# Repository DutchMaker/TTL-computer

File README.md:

# 74xx Computer

My attempt at building a computer from scratch with 74xxx logic chips.  

## Project Shelved!

I have abandoned this project, but only to reboot it with a different approach.  
Make sure to check **[The DM-02 Computer](https://github.com/DutchMaker/DM-02)** which is my second attempt at a computer from scratch!

## Status as of September 4th, 2019:

[**General architecture**](https://github.com/DutchMaker/TTL-computer/blob/master/Documentation/Architecture.pdf) has been worked out as high level schematic.  

Worked on **instruction set, micro code, module documentation & general notes** from time to time (see: [Documentation](https://github.com/DutchMaker/TTL-computer/tree/master/Documentation)). Only thing missing right now is some documentation on each of the modules. 

The entire computer has been built in [**Logisim**](https://github.com/DutchMaker/TTL-computer/tree/master/Documentation/Logisim) to verify that the way I had everything in mind is actually going to work.

I've built a [**microcode compiler**](https://github.com/DutchMaker/TTL-computer/tree/master/Code/Microcode) for the Controller's ROM image. This takes a source file which defines all the microcode and compiles it into a binary image that is loaded into the microcode ROM.

The 74xx Computer's **instruction set** has been implemented, its **[assembly language](https://github.com/DutchMaker/TTL-computer/blob/master/Documentation/74xx-Assembly-Language.md)** is fully documented and I've built an [**assembler**](https://github.com/DutchMaker/TTL-computer/tree/master/Code/Assembler) to convert assembly programs to machine code.

[**Circuit diagrams and PCBs**](https://github.com/DutchMaker/TTL-computer/tree/master/Circuits) have all been designed in KiCad and have been or are currently being produced:

- [x] Clock (*built and tested*)
- [x] Registers (*built and tested*)
- [x] ALU (*built and tested*)
- [x] Program Counter (*built and tested*)
- [x] Stack Pointer (*built and tested*)
- [x] Flags register (*built and tested*)
- [x] Memory (*built and tested*)
- [x] Memory Access Register (*built and tested*)
- [ ] Controller (*redesigned circuit to account for reset ciruitry - waiting for PCB production*)
- [x] Main Board ( *built and tested*)

## TODO's / Plans:

- Build the computer in real life (**IN PROGRESS**)
  - First revision is based on separate PCBs that are all connected together by one large main PCB.
  - If all works out, there may be a second revision will be one large PCB that contains all modules as one circuit.
- Write additional/updated documentation on all modules.

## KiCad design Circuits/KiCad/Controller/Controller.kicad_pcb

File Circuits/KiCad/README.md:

# KiCad projects

- Add `./Libraries/74xx-Computer-Symbols.lib` as global Symbol library to KiCad (Eeschema)
- Add `./Libraries` as global Footprint library to KiCad (Pcbnew)
- PCBs are initially autorouted using `./Libraries/freeRouting.jar` and traces are enhanced manually

### Known deviations/errors in current Schematic/PCB files

There are a number of deviations and errors that were found in schematic/PCB designs after PCB production. They are listed here if they were not fixed in the schematic/PCB design files.

- **ALU:** LED bar graph for AX (_BAR1_) and AY (_BAR2_) have swapped places on the PCB.
- **ALU:** Cn input needs to be inverted.
- This is added to the main board because ALU PCB was already produced and there were no available NOT gates available.
- **ALU:** Outer margin varies from other boards.
- **Flags Register:** U6 and U7 (74x74) ~PRE pins (4 and 10) are floating. They must be tied to +5V otherwise the chip does not function properly.
- **Memory & Memory Access Register:** The switches used for SW1 to SW8 briefly short out the circuit while switching. This reset the entire computer. Solved this by removing the connection to ground and adding 10k pull-down resistors between the data lines and ground.
- **Memory:** RAM should write when clock pulse is high. Otherwise manual input is difficult because that relies on single stepping the clock. Solved this by feeding the clock signal through U1 (74x04) before connecting it to U4A (74x32).
- **Main Board:** Current main board PCB design does not fit the current instruction register PCB - only the improvised one that I've built.
- **Controller:** U9 (74x74) ground pin is not connected. Also ~PRE pin (4) is floating and must be tied to +5V.
- **Controller & Memory**: Drill holes for ZIF socket are too narrow (need to be 1mm).
- **Main Board:** Forgot to add LED bar to display data bus contents.
- **Main Board:** Forgot to add one or more expansion ports.
- **Main Board:** Need pull-down resistors on the data bus
- **Controller**: There is an issue with powering up the controller: its initial state has all control lines enabled. This messes up the state of other modules.
  - Needs pull-down/up resistors on control lines for initial state of modules (reset state) - this is improvised on the main board now. We also must have a boot/reset procedure, something like: 
    - First all control line output is high impedance (this resets all modules because of the pull-down/up resistors that determine initial state). Will probably do this by cutting power to the controller during boot.
    - Then the controller is powered up and it needs to load microcode address 0
    - Then it can start processing instructions

### Suggested improvements

- Clock: Use a bigger push switch for single stepping
  - Add a *continue* option in order to continue execution after a HALT instruction.
- When all modules are built and tested, combine them into a single PCB.
  - I may decide to never do this and just start designing the next version of the CPU.
- Add decoupling caps (have only been added to main board now)
- Improve silk screen documentation
- Databus LEDs missing on Main Board
- Add hex decoders to registers / memory.
  - Add switch to disable output?
- ADC and SUBC instructions should take the carry flag into account
  - SUBC may be renamed to SUBB (borrow)

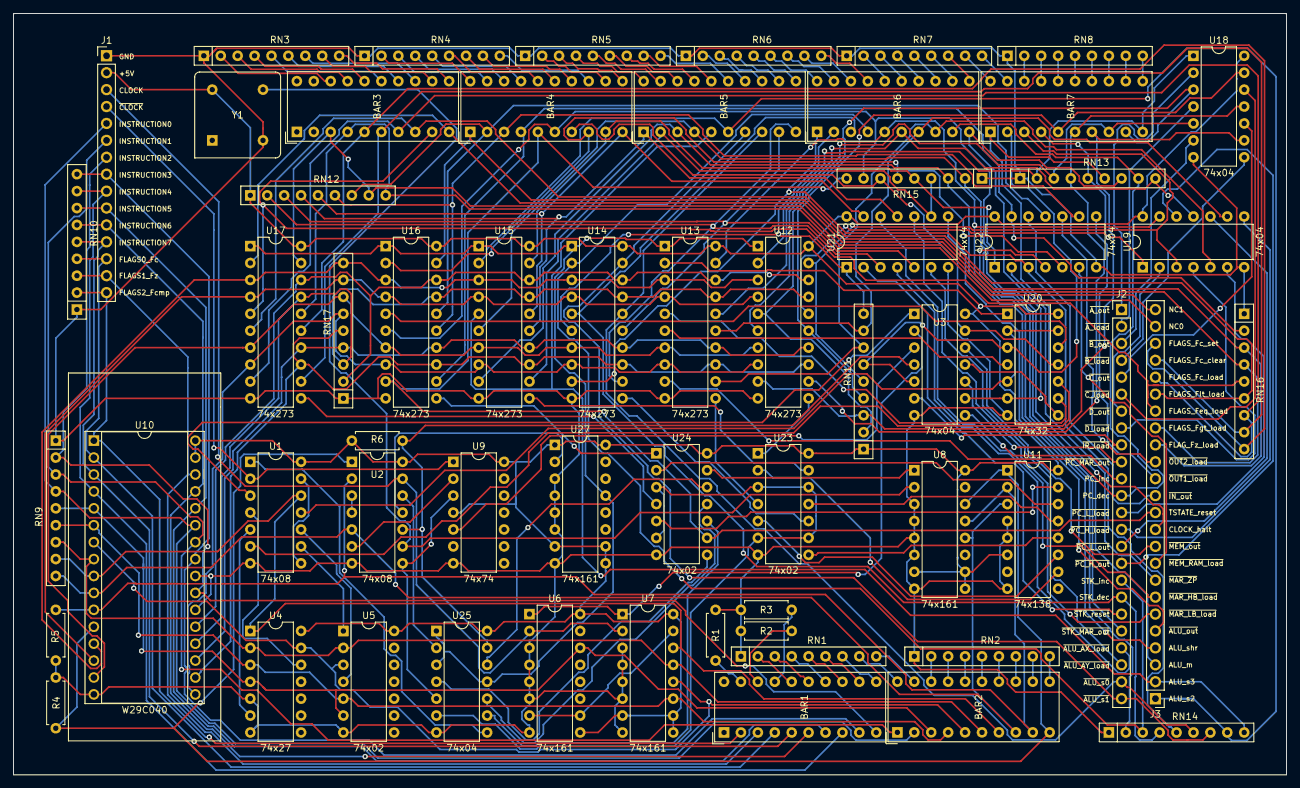
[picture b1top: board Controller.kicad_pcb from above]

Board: 2 copper layers, 191.1 x 114.3 mm, 60 parts (0 on the bottom side), 216 nets.

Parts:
BAR1, BAR2, BAR3, BAR4, BAR5, BAR6, BAR7: HDSP-4830_2; Bar-Graph-10
J1: Conn_01x15_Male; PinHeader_1x15_P2.54mm_Vertical
J2, J3: Conn_01x24_Male; PinHeader_1x24_P2.54mm_Vertical
R1, R2, R4, R5: R; R_Axial_DIN0207_L6.3mm_D2.5mm_P7.62mm_Horizontal
R3: 470; R_Axial_DIN0207_L6.3mm_D2.5mm_P7.62mm_Horizontal
R6: 10K; R_Axial_DIN0207_L6.3mm_D2.5mm_P7.62mm_Horizontal
RN1, RN2, RN3, RN4, RN5, RN6, RN7, RN8: 470; R_Array_SIP9
RN9, RN10, RN11, RN12, RN13, RN14, RN15, RN16, RN17: 10K; R_Array_SIP9
U1, U2: 74x08; DIP-14_W7.62mm
U3, U18, U19, U21, U22, U25: 74x04; DIP-14_W7.62mm
U4: 74x27; DIP-14_W7.62mm
U5, U23, U24: 74x02; DIP-14_W7.62mm
U6, U7, U8, U27: 74x161; DIP-16_W7.62mm
U9: 74x74; DIP-14_W7.62mm
U10: W29C040; ZIF-32_Socket
U11: 74x138; DIP-16_W7.62mm
U12, U13, U14, U15, U16, U17: 74x273; DIP-20_W7.62mm
U20: 74x32; DIP-14_W7.62mm
Y1: 8 MHz (max. 10 MHz); Oscillator_DIP-8_v2

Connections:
+5V: J1.2, R6.1, RN11.1, RN12.1, U1.14, U2.14, U3.14, U4.14, U5.14, U6.9, U6.16, U7.7, U7.9, U7.10, U7.16, U8.7, U8.9, U8.10, U8.16, U9.4, U9.14, U10.31, U10.32, U11.6, U11.16, U12.20, U13.20, U14.20, U15.20, U16.20, U17.20, U18.14, U19.14, U20.14, U21.14, U22.14, U23.14, U24.14, U25.14, U27.1, U27.7, U27.9, U27.10, U27.16, Y1.1
ALU_AX_load: BAR5.10, RN12.2, U14.12, U21.3
ALU_AY_load: BAR5.9, RN12.3, U14.15, U21.5
ALU_m: BAR5.4, J3.3, RN15.2, U15.6
ALU_out: BAR5.2, RN15.4, U15.12, U21.9
ALU_s0: BAR5.8, J2.23, RN14.6, U14.16
ALU_s1: BAR5.7, J2.24, RN14.7, U14.19
ALU_s2: BAR5.6, J3.1, RN14.8, U15.2
ALU_s3: BAR5.5, J3.2, RN14.9, U15.5
ALU_shr: BAR5.3, J3.4, RN15.3, U15.9
A_load: BAR7.9, RN11.2, U12.5, U18.3
A_out: BAR7.10, RN13.2, U12.2, U18.1
BANK0: BAR2.10, R4.1, U2.1, U8.14, U10.12, U11.1
BANK1: BAR2.9, R5.1, U2.2, U8.13, U10.11, U11.2
BANK2: BAR2.8, RN9.9, U2.5, U8.12, U10.10, U11.3
B_load: BAR7.7, RN11.3, U12.9, U18.9
B_out: BAR7.8, RN13.3, U12.6, U18.5
CLOCK: J1.3, U2.13, U6.2, U7.2
CLOCK_INTERNAL: U2.9, U8.2, Y1.3
CLOCK_halt: BAR4.6, J3.11, RN15.8, U16.6
C_load: BAR7.5, RN11.4, U12.15, U18.13
C_out: BAR7.6, RN13.4, U12.12, U18.11
DATA0: RN17.9, U10.13, U12.3, U13.3, U14.3, U15.3, U16.3, U17.3
DATA1: RN17.8, U10.14, U12.4, U13.4, U14.4, U15.4, U16.4, U17.4
DATA2: RN17.7, U10.15, U12.7, U13.7, U14.7, U15.7, U16.7, U17.7
DATA3: RN17.6, U10.17, U12.8, U13.8, U14.8, U15.8, U16.8, U17.8
DATA4: RN17.5, U10.18, U12.13, U13.13, U14.13, U15.13, U16.13, U17.13
DATA5: RN17.4, U10.19, U12.14, U13.14, U14.14, U15.14, U16.14, U17.14
DATA6: RN17.3, U10.20, U12.17, U13.17, U14.17, U15.17, U16.17, U17.17
DATA7: RN17.2, U10.21, U12.18, U13.18, U14.18, U15.18, U16.18, U17.18
D_load: BAR7.3, RN11.5, U12.19, U19.3
D_out: BAR7.4, RN13.5, U12.16, U19.1
EN0: U11.10, U23.2
EN1: U11.11, U23.5
EN2: U11.12, U23.8
EN3: U11.13, U23.11
EN4: U11.14, U24.2
EN5: U11.15, U24.5
FLAGS0_Fc: BAR1.4, J1.13, RN10.4, U10.2
FLAGS1_Fz: BAR1.3, J1.14, RN10.3, U10.30
FLAGS2_Fcmp: BAR1.2, J1.15, RN10.2, U10.1
FLAGS_Fc_clear: BAR3.6, J3.21, RN16.8, U17.12
FLAGS_Fc_load: BAR3.7, J3.20, RN16.7, U17.9
FLAGS_Fc_set: BAR3.5, J3.22, RN16.9, U17.15
FLAGS_Feq_load: BAR3.9, J3.18, RN16.5, U17.5
FLAGS_Fgt_load: BAR3.10, J3.17, RN16.4, U17.2
FLAGS_Flt_load: BAR3.8, J3.19, RN16.6, U17.6
FLAGS_Fz_load: BAR4.1, J3.16, RN16.3, U16.19
GND: J1.1, R1.1, R2.1, R3.1, R4.2, R5.2, RN1.1, RN2.1, RN3.1, RN4.1, RN5.1, RN6.1, RN7.1, RN8.1, RN9.1, RN10.1, RN13.1, RN14.1, RN15.1, RN16.1, RN17.1, U1.7, U2.7, U3.7, U4.5, U4.7, U5.7, U6.3, U6.4, U6.5, U6.6, U6.8, U7.3, U7.4, U7.5, U7.6, U7.8, U8.3, U8.4, U8.5, U8.6, U8.8, U9.7, U10.16, U10.22, U10.24, U11.4, U11.5, U11.8, U12.10, U13.10, U14.10, U15.10, U16.10, U17.10, U18.7, U19.7, U20.7, U21.7, U22.7, U23.7, U24.7, U25.7, U27.3, U27.4, U27.5, U27.6, U27.8, Y1.2
INSTRUCTION0: BAR2.2, J1.5, RN9.4, U10.27
INSTRUCTION1: BAR2.1, J1.6, RN9.3, U10.26
INSTRUCTION2: BAR1.10, J1.7, RN9.2, U10.23
INSTRUCTION3: BAR1.9, J1.8, RN10.9, U10.25
INSTRUCTION4: BAR1.8, J1.9, RN10.8, U10.4
INSTRUCTION5: BAR1.7, J1.10, RN10.7, U10.28
INSTRUCTION6: BAR1.6, J1.11, RN10.6, U10.29
INSTRUCTION7: BAR1.5, J1.12, RN10.5, U10.3
IN_out: BAR4.4, RN16.2, U16.12, U22.13
IR_load: U13.2, U20.1
IR_load_LED: BAR7.2, RN11.6, U3.5, U20.3
MAR_HB_load: BAR4.10, RN12.5, U15.16, U21.13
MAR_LB_load: BAR5.1, RN12.4, U15.15, U21.11
MAR_ZP: BAR4.9, RN15.5, U15.19, U22.1
MEM_RAM_load: BAR4.8, RN15.6, U16.2, U22.5
MEM_out: U16.5, U20.12
MEM_out_LED: BAR4.7, RN15.7, U3.13, U20.11
NC0: BAR3.4, J3.23, RN12.9, U17.16
NC1: BAR3.3, J3.24, RN12.8, U17.19
unnamed: BAR1.11, RN1.7
unnamed: BAR1.12, RN1.6
unnamed: BAR1.13, RN1.5
unnamed: BAR1.14, RN1.4
unnamed: BAR1.15, RN1.3
unnamed: BAR1.16, RN1.2
unnamed: BAR1.17, R3.2
unnamed: BAR1.18, R2.2
unnamed: BAR1.19, R1.2
unnamed: BAR2.11, RN2.9
unnamed: BAR2.12, RN2.8
unnamed: BAR2.13, RN2.7
unnamed: BAR2.14, RN2.6
unnamed: BAR2.15, RN2.5
unnamed: BAR2.16, RN2.4
unnamed: BAR2.17, RN2.3
unnamed: BAR2.18, RN2.2
unnamed: BAR2.19, RN1.9
unnamed: BAR2.20, RN1.8
unnamed: BAR3.11, RN3.9
unnamed: BAR3.12, RN3.8
unnamed: BAR3.13, RN3.7
unnamed: BAR3.14, RN3.6
unnamed: BAR3.15, RN3.5
unnamed: BAR3.16, RN3.4
unnamed: BAR3.17, RN3.3
unnamed: BAR3.18, RN3.2
unnamed: BAR4.11, RN5.3
unnamed: BAR4.12, RN5.2
unnamed: BAR4.13, RN4.9
unnamed: BAR4.14, RN4.8
unnamed: BAR4.15, RN4.7
unnamed: BAR4.16, RN4.6
unnamed: BAR4.17, RN4.5
unnamed: BAR4.18, RN4.4
unnamed: BAR4.19, RN4.3
unnamed: BAR4.20, RN4.2
unnamed: BAR5.11, RN6.5
unnamed: BAR5.12, RN6.4
unnamed: BAR5.13, RN6.3
unnamed: BAR5.14, RN6.2
unnamed: BAR5.15, RN5.9
unnamed: BAR5.16, RN5.8
unnamed: BAR5.17, RN5.7
unnamed: BAR5.18, RN5.6
unnamed: BAR5.19, RN5.5
unnamed: BAR5.20, RN5.4
unnamed: BAR6.11, RN7.7
unnamed: BAR6.12, RN7.6
unnamed: BAR6.13, RN7.5
unnamed: BAR6.14, RN7.4
unnamed: BAR6.15, RN7.3
unnamed: BAR6.16, RN7.2
unnamed: BAR6.17, RN6.9
unnamed: BAR6.18, RN6.8
unnamed: BAR6.19, RN6.7
unnamed: BAR6.20, RN6.6
unnamed: BAR7.11, RN8.9
unnamed: BAR7.12, RN8.8
unnamed: BAR7.13, RN8.7
unnamed: BAR7.14, RN8.6
unnamed: BAR7.15, RN8.5
unnamed: BAR7.16, RN8.4
unnamed: BAR7.17, RN8.3
unnamed: BAR7.18, RN8.2
unnamed: BAR7.19, RN7.9
unnamed: BAR7.20, RN7.8
unnamed: U1.1, U25.8
unnamed: U1.3, U3.1
unnamed: U1.4, U4.12
unnamed: U1.5, U4.6
unnamed: U1.9, U5.1
unnamed: U1.10, U5.4
unnamed: U1.8, U1.13
unnamed: U2.3, U2.4
unnamed: U2.6, U9.2
unnamed: U2.8, U9.3, U25.5
unnamed: U2.11, U27.2
unnamed: U2.12, U25.2
unnamed: U3.2, U6.1, U7.1
unnamed: U3.3, U9.5
unnamed: U6.7, U6.10, U7.15
unnamed: U12.11, U23.1
unnamed: U13.11, U23.4
unnamed: U14.11, U23.10
unnamed: U15.11, U23.13
unnamed: U16.11, U24.1
unnamed: U17.11, U24.4
unnamed: U23.3, U23.6, U23.9, U23.12, U24.3, U24.6, U25.6
unnamed: U24.8, U25.4
unnamed: U24.10, U25.9
unnamed: U24.11, U25.10
unnamed: U24.12, U25.12
unnamed: U8.1, U24.13
OUT1_load: BAR4.3, RN12.6, U16.15, U22.9
OUT2_load: BAR4.2, RN12.7, U16.16, U22.11
PC_H_load: BAR6.7, RN11.8, U13.15, U19.9
PC_H_out: BAR6.5, RN14.2, U13.19, U19.13
PC_L_load: BAR6.8, RN11.7, U13.12, U19.5
PC_L_out: BAR6.6, RN13.9, U13.16, U19.11
PC_MAR_out: U13.5, U20.9
PC_MAR_out_LED: BAR7.1, RN13.6, U3.11, U20.8
PC_dec: BAR6.9, J2.12, RN13.8, U13.9
PC_inc: J2.11, U3.8
PC_inc_: U13.6, U20.4
PC_inc_LED: BAR6.10, RN13.7, U3.9, U20.6
RUNNING: U12.1, U13.1, U14.1, U15.1, U16.1, U17.1, U25.1, U25.3, U25.11, U27.13
STK_MAR_out: BAR6.1, RN14.5, U14.9, U22.3
STK_dec: BAR6.3, J2.18, RN14.4, U14.5
STK_inc: BAR6.4, J2.17, RN14.3, U14.2
STK_reset: BAR6.2, RN11.9, U14.6, U21.1
TSTATE0: BAR2.7, RN9.8, U1.12, U4.1, U7.14, U10.9
TSTATE1: BAR2.6, RN9.7, U4.2, U5.2, U7.13, U10.8
TSTATE2: BAR2.5, U4.13, U5.3, U7.12, U10.7
TSTATE3: BAR2.4, RN9.6, U4.3, U5.5, U7.11, U10.6
TSTATE4: BAR2.3, RN9.5, U4.4, U5.6, U6.14, U10.5
TSTATE=0: U1.6, U20.10
TSTATE=1: U1.11, U20.2, U20.5, U20.13
TSTATE_reset: BAR4.5, J3.12, RN15.9, U16.9, U24.9
~ALU_AX_load: J2.21, U21.4
~ALU_AY_load: J2.22, U21.6
~ALU_out: J3.5, U21.8
~A_load: J2.2, U18.4
~A_out: J2.1, U18.2
~B_load: J2.4, U18.8
~B_out: J2.3, U18.6
~CLOCK: J1.4, U1.2, U9.1
~C_load: J2.6, U18.12
~C_out: J2.5, U18.10
~D_load: J2.8, U19.4
~D_out: J2.7, U19.2
~IN_out: J3.13, U22.12
~IR_load: J2.9, U3.6
~LOAD_DONE: R6.2, U2.10, U3.4, U25.13
~MAR_HB_load: J3.7, U21.12
~MAR_LB_load: J3.6, U21.10
~MAR_ZP: J3.8, U22.2
~MEM_RAM_load: J3.9, U22.6
~MEM_out: J3.10, U3.12
~OUT1_load: J3.14, U22.8
~OUT2_load: J3.15, U22.10
~PC_H_load: J2.14, U19.8
~PC_H_out: J2.16, U19.12
~PC_L_load: J2.13, U19.6
~PC_L_out: J2.15, U19.10
~PC_MAR_out: J2.10, U3.10
~STK_MAR_out: J2.20, U22.4
~STK_reset: J2.19, U21.2

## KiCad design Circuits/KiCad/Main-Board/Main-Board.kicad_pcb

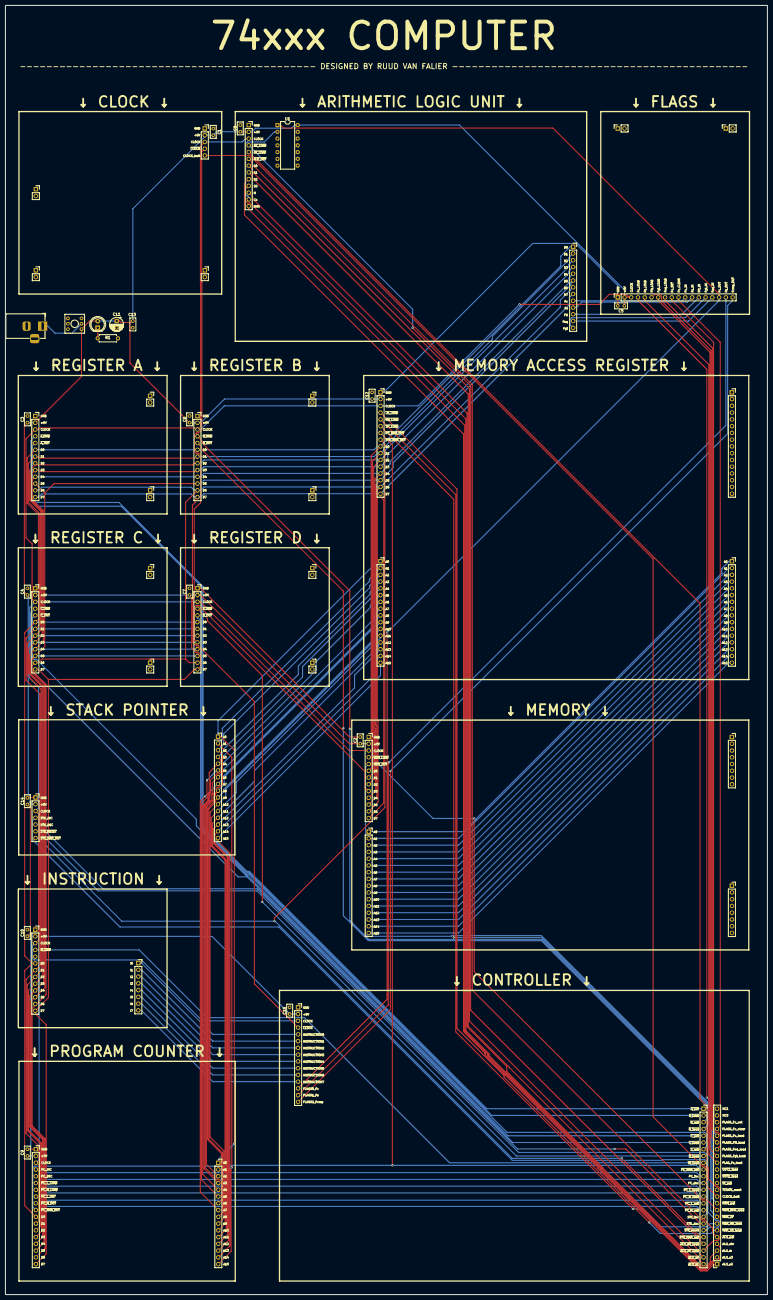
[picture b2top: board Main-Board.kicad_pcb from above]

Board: 2 copper layers, 286.4 x 484.5 mm, 58 parts (0 on the bottom side), 105 nets.

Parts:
C1, C2, C3, C4, C5, C6, C7, C8, C9, C10, C12, C13, C14, C15: 100 nF; C_Rect_L4.6mm_W2.0mm_P2.50mm_MKS02_FKP02
C11: 100 uF; CP_Radial_D5.0mm_P2.50mm
D1: LED; LED_D5.0mm
J1: CLOCK; PinSocket_1x05_P2.54mm_Vertical
J2: MEMORY_0; PinSocket_1x13_P2.54mm_Vertical
J3: REGISTER-A; PinSocket_1x13_P2.54mm_Vertical
J4: REGISTER-C; PinSocket_1x13_P2.54mm_Vertical
J5: FLAGS-REGISTER; PinSocket_1x18_P2.54mm_Vertical
J6: MEMORY_1; PinSocket_1x16_P2.54mm_Vertical
J7: REGISTER-B; PinSocket_1x13_P2.54mm_Vertical
J8: REGISTER-D; PinSocket_1x13_P2.54mm_Vertical
J9: PROGRAM-COUNTER_0; PinSocket_1x18_P2.54mm_Vertical
J10: ALU_0; PinSocket_1x13_P2.54mm_Vertical
J11: ALU_1; PinSocket_1x13_P2.54mm_Vertical
J12: IR_0; PinSocket_1x13_P2.54mm_Vertical
J13: MAR_0; PinSocket_1x16_P2.54mm_Vertical
J14: PROGRAM-COUNTER_1; PinSocket_1x16_P2.54mm_Vertical
J15: IR_1; PinSocket_1x08_P2.54mm_Vertical
J16: SP_0; PinSocket_1x07_P2.54mm_Vertical
J17: MAR_1_ADDRESS-IN; PinSocket_1x16_P2.54mm_Vertical
J18: SP_1_MEMORY-ADDRESS; PinSocket_1x16_P2.54mm_Vertical
J19: MAR_2_ADDRESS-OUT; PinSocket_1x16_P2.54mm_Vertical
J20: CONTROLLER_0; PinSocket_1x15_P2.54mm_Vertical
J21: CONTROLLER_1; PinSocket_1x24_P2.54mm_Vertical
J22: CONTROLLER_2; PinSocket_1x24_P2.54mm_Vertical
J23: Barrel_Jack; BarrelJack_Horizontal
J24: CLOCK_1; PinSocket_1x02_P2.54mm_Vertical
J25: CLOCK_2; PinSocket_1x02_P2.54mm_Vertical
J26: CLOCK_3; PinSocket_1x02_P2.54mm_Vertical
J27: FLAGS-REGISTER_1; PinSocket_1x02_P2.54mm_Vertical
J28: FLAGS-REGISTER_2; PinSocket_1x02_P2.54mm_Vertical
J29: MEMORY_2; PinSocket_1x08_P2.54mm_Vertical
J30: MEMORY_3; PinSocket_1x08_P2.54mm_Vertical
J31: MAR_3; PinSocket_1x16_P2.54mm_Vertical
J32: REGISTER-A_1; PinSocket_1x02_P2.54mm_Vertical
J33: REGISTER-A_2; PinSocket_1x02_P2.54mm_Vertical
J34: REGISTER-C_1; PinSocket_1x02_P2.54mm_Vertical
J35: REGISTER-C_2; PinSocket_1x02_P2.54mm_Vertical
J36: REGISTER-B_1; PinSocket_1x02_P2.54mm_Vertical
J37: REGISTER-B_2; PinSocket_1x02_P2.54mm_Vertical
J38: REGISTER-D_1; PinSocket_1x02_P2.54mm_Vertical
J39: REGISTER-D_2; PinSocket_1x02_P2.54mm_Vertical
R1: 470; R_Axial_DIN0207_L6.3mm_D2.5mm_P7.62mm_Horizontal
SW1: SW_Push_SPDT; Switch
U1: 74x04; DIP-14_W7.62mm

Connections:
+5V: C1.2, C2.2, C3.2, C4.2, C5.2, C6.2, C7.2, C8.2, C9.2, C10.2, C11.1, C12.2, C13.1, C14.2, C15.2, D1.2, J1.2, J2.2, J3.2, J4.2, J5.2, J7.2, J8.2, J9.2, J10.2, J12.2, J13.2, J16.2, J20.2, SW1.3, U1.14
A0: J14.1, J17.1, J18.1
A1: J14.2, J17.2, J18.2
A2: J14.3, J17.3, J18.3
A3: J14.4, J17.4, J18.4
A4: J14.5, J17.5, J18.5
A5: J14.6, J17.6, J18.6
A6: J14.7, J17.7, J18.7
A7: J14.8, J17.8, J18.8
A8: J14.9, J17.9, J18.9
A9: J14.10, J17.10, J18.10
A10: J14.11, J17.11, J18.11
A11: J14.12, J17.12, J18.12
A12: J14.13, J17.13, J18.13
A13: J14.14, J17.14, J18.14
A14: J14.15, J17.15, J18.15
A15: J14.16, J17.16, J18.16
ALU_Cn: J10.12, U1.2
ALU_m: J10.11, J22.3
ALU_s0: J10.7, J21.23
ALU_s1: J10.8, J21.24
ALU_s2: J10.9, J22.1
ALU_s3: J10.10, J22.2
ALU_shr: J10.13, J22.4
CLOCK: J1.3, J2.3, J3.3, J4.3, J5.3, J7.3, J8.3, J9.3, J10.3, J12.3, J13.3, J16.3, J20.3
CLOCK_halt: J1.5, J22.11
DATA_BUS0: J2.6, J3.6, J4.6, J7.6, J8.6, J9.11, J11.1, J12.6, J13.9
DATA_BUS1: J2.7, J3.7, J4.7, J7.7, J8.7, J9.12, J11.2, J12.7, J13.10
DATA_BUS2: J2.8, J3.8, J4.8, J7.8, J8.8, J9.13, J11.3, J12.8, J13.11
DATA_BUS3: J2.9, J3.9, J4.9, J7.9, J8.9, J9.14, J11.4, J12.9, J13.12
DATA_BUS4: J2.10, J3.10, J4.10, J7.10, J8.10, J9.15, J11.5, J12.10, J13.13
DATA_BUS5: J2.11, J3.11, J4.11, J7.11, J8.11, J9.16, J11.6, J12.11, J13.14
DATA_BUS6: J2.12, J3.12, J4.12, J7.12, J8.12, J9.17, J11.7, J12.12, J13.15
DATA_BUS7: J2.13, J3.13, J4.13, J7.13, J8.13, J9.18, J11.8, J12.13, J13.16
FLAGS_Fc_clear: J5.10, J22.21
FLAGS_Fc_load: J5.4, J22.20
FLAGS_Fc_set: J5.9, J22.22
FLAGS_Feq_load: J5.8, J22.18
FLAGS_Fgt_load: J5.7, J22.17
FLAGS_Flt_load: J5.6, J22.19
FLAGS_Fz_load: J5.5, J22.16
Fc_in: J5.11, J11.9
Fc_out: J5.16, J20.13, U1.1
Fcmp_out: J5.18, J20.15
Feq_in: J5.15, J11.12
Fgt_in: J5.14, J11.13
Flt_in: J5.13, J11.11
Fz_in: J5.12, J11.10
Fz_out: J5.17, J20.14
GND: C1.1, C2.1, C3.1, C4.1, C5.1, C6.1, C7.1, C8.1, C9.1, C10.1, C11.2, C12.1, C13.2, C14.1, C15.1, J1.1, J2.1, J3.1, J4.1, J5.1, J7.1, J8.1, J9.1, J10.1, J12.1, J13.1, J16.1, J20.1, J23.2, R1.2, U1.7
INSTRUCTION0: J15.1, J20.5
INSTRUCTION1: J15.2, J20.6
INSTRUCTION2: J15.3, J20.7
INSTRUCTION3: J15.4, J20.8
INSTRUCTION4: J15.5, J20.9
INSTRUCTION5: J15.6, J20.10
INSTRUCTION6: J15.7, J20.11
INSTRUCTION7: J15.8, J20.12
MAR0: J6.1, J19.1
MAR1: J6.2, J19.2
MAR2: J6.3, J19.3
MAR3: J6.4, J19.4
MAR4: J6.5, J19.5
MAR5: J6.6, J19.6
MAR6: J6.7, J19.7
MAR7: J6.8, J19.8
MAR8: J6.9, J19.9
MAR9: J6.10, J19.10
MAR10: J6.11, J19.11
MAR11: J6.12, J19.12
MAR12: J6.13, J19.13
MAR13: J6.14, J19.14
MAR14: J6.15, J19.15
MAR15: J6.16, J19.16
unnamed: D1.1, R1.1
unnamed: J23.1, SW1.2
PC_dec: J9.5, J21.12
PC_inc: J9.4, J21.11
STK_dec: J16.5, J21.18
STK_inc: J16.4, J21.17
~ALU_AX_load: J10.4, J21.21
~ALU_AY_load: J10.5, J21.22
~ALU_out: J10.6, J22.5
~A_load: J3.4, J21.2
~A_out: J3.5, J21.1
~B_load: J7.4, J21.4
~B_out: J7.5, J21.3
~CLOCK: J1.4, J20.4
~C_load: J4.4, J21.6
~C_out: J4.5, J21.5
~D_load: J8.4, J21.8
~D_out: J8.5, J21.7
~IR_load: J12.4, J21.9
~MAR_HB_load: J13.5, J22.7
~MAR_LB_load: J13.4, J22.6
~MAR_ZP: J13.6, J22.8
~MEM_RAM_load: J2.4, J22.9
~MEM_out: J2.5, J22.10
~PC_H_load: J9.7, J21.14
~PC_H_out: J9.9, J21.16
~PC_L_load: J9.6, J21.13
~PC_L_out: J9.8, J21.15
~PC_MAR_out: J9.10, J13.7, J21.10
~STK_MAR_out: J13.8, J16.7, J21.20
~STK_reset: J16.6, J21.19

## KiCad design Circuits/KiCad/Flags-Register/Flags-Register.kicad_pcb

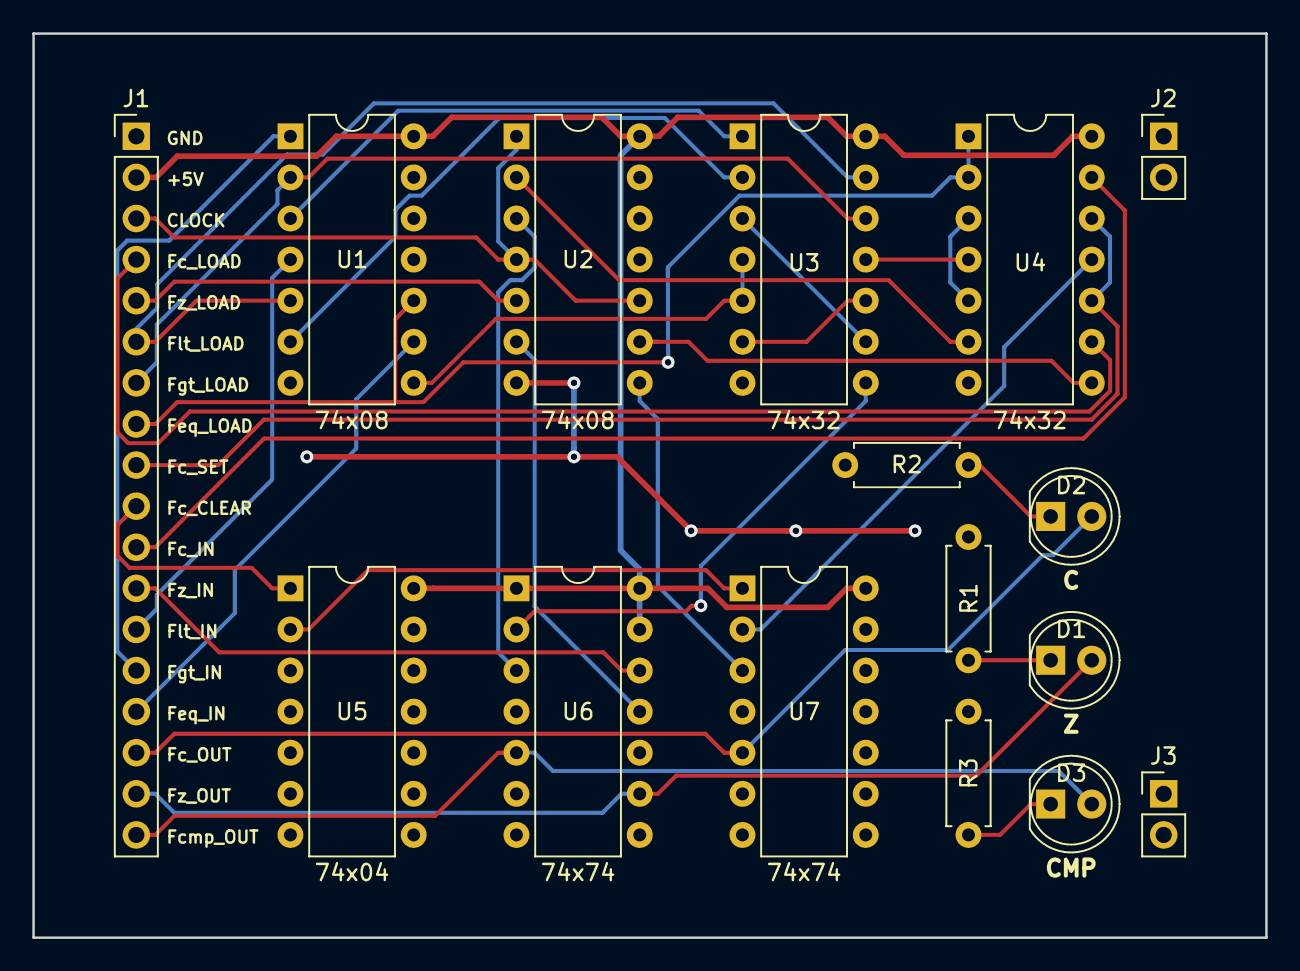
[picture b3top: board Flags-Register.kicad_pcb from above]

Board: 2 copper layers, 76.2 x 55.9 mm, 16 parts (0 on the bottom side), 36 nets.

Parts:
D1: Z; LED_D5.0mm
D2: C; LED_D5.0mm
D3: CMP; LED_D5.0mm
J1: Conn_01x18_Male; PinHeader_1x18_P2.54mm_Vertical
J2, J3: Conn_01x02_Male; PinHeader_1x02_P2.54mm_Vertical
R1, R2, R3: 470; R_Axial_DIN0207_L6.3mm_D2.5mm_P7.62mm_Horizontal
U1, U2: 74x08; DIP-14_W7.62mm
U3, U4: 74x32; DIP-14_W7.62mm
U5: 74x04; DIP-14_W7.62mm
U6, U7: 74x74; DIP-14_W7.62mm

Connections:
+5V: J1.2, U1.14, U2.14, U3.14, U4.14, U5.14, U6.1, U6.13, U6.14, U7.14
CLOCK: J1.3, U2.1, U2.4, U2.10
Fc_CLEAR: J1.10, U5.1
Fc_IN: J1.11, U4.13
Fc_LOAD: J1.4, U4.9
Fc_OUT: D2.2, J1.16, U7.5
Fc_SET: J1.9, U4.10, U4.12
Fcmp_OUT: D3.2, J1.18, U6.5
Feq_IN: J1.15, U1.9
Feq_LOAD: J1.8, U1.10, U4.1, U4.2
Fgt_IN: J1.14, U1.1
Fgt_LOAD: J1.7, U1.2, U3.12
Flt_IN: J1.13, U1.4
Flt_LOAD: J1.6, U1.5, U3.13
Fz_IN: J1.12, U6.12
Fz_LOAD: J1.5, U2.5
Fz_OUT: D1.2, J1.17, U6.9
GND: J1.1, R1.2, R2.2, R3.2, U1.7, U2.7, U3.7, U4.7, U5.7, U6.7, U7.7
unnamed: D1.1, R1.1
unnamed: D2.1, R2.1
unnamed: D3.1, R3.1
unnamed: U1.3, U3.1
unnamed: U1.6, U3.2
unnamed: U1.8, U3.4, U3.5
unnamed: U2.2, U4.6
unnamed: U2.3, U6.3
unnamed: U2.6, U6.11
unnamed: U2.8, U7.3
unnamed: U2.9, U4.8
unnamed: U3.3, U3.9
unnamed: U3.8, U6.2
unnamed: U3.6, U3.10
unnamed: U3.11, U4.4
unnamed: U4.3, U4.5
unnamed: U4.11, U7.2
unnamed: U5.2, U7.1

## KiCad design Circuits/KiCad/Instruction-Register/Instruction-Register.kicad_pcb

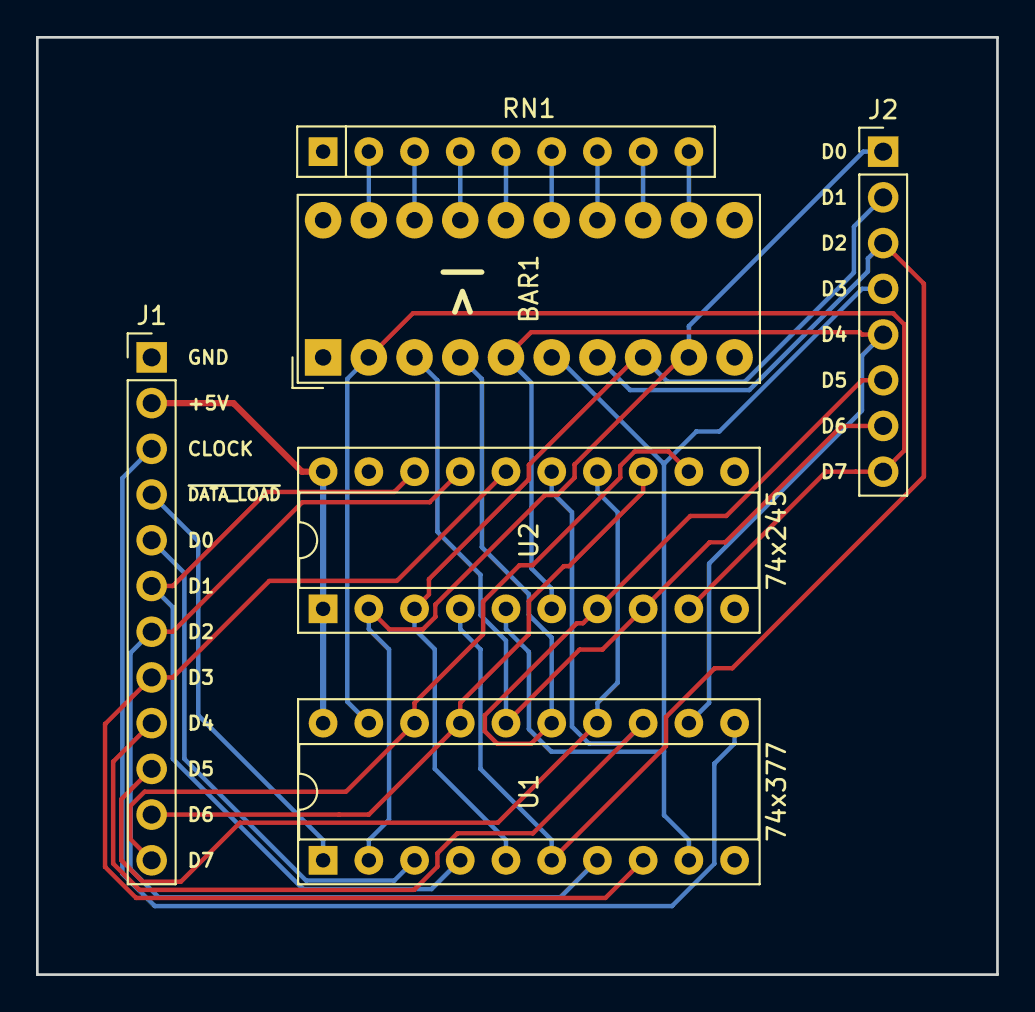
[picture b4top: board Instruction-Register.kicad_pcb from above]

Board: 2 copper layers, 53.3 x 52.1 mm, 6 parts (0 on the bottom side), 28 nets.

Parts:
BAR1: LED-BAR; HDSP-4830
J1: Conn_01x12_Male; PinHeader_1x12_P2.54mm_Vertical
J2: Conn_01x08_Male; PinHeader_1x08_P2.54mm_Vertical
RN1: 470; R_Array_SIP9
U1: 74x377; DIP-20_W7.62mm_Socket
U2: 74x245; DIP-20_W7.62mm_Socket

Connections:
+5V: J1.2, U1.20, U2.1, U2.20
CLOCK: J1.3, U1.11
GND: J1.1, RN1.1, U1.10, U2.10
unnamed: BAR1.2, J2.8, U1.19, U2.9
unnamed: BAR1.3, J2.7, U1.16, U2.8
unnamed: BAR1.4, J2.6, U1.15, U2.7
unnamed: BAR1.5, J2.5, U1.12, U2.6
unnamed: BAR1.6, J2.4, U1.9, U2.5
unnamed: BAR1.7, J2.3, U1.6, U2.4
unnamed: BAR1.8, J2.2, U1.5, U2.3
unnamed: BAR1.9, J2.1, U1.2, U2.2
unnamed: BAR1.12, RN1.9
unnamed: BAR1.13, RN1.8
unnamed: BAR1.14, RN1.7
unnamed: BAR1.15, RN1.6
unnamed: BAR1.16, RN1.5
unnamed: BAR1.17, RN1.4
unnamed: BAR1.18, RN1.3
unnamed: BAR1.19, RN1.2
unnamed: J1.5, U1.3
unnamed: J1.6, U1.4, U2.18
unnamed: J1.7, U1.7, U2.17
unnamed: J1.8, U1.8, U2.16
unnamed: J1.9, U1.13, U2.15
unnamed: J1.10, U1.14, U2.14
unnamed: J1.11, U1.17, U2.13
unnamed: J1.12, U1.18, U2.12
~DATA_LOAD: J1.4, U1.1

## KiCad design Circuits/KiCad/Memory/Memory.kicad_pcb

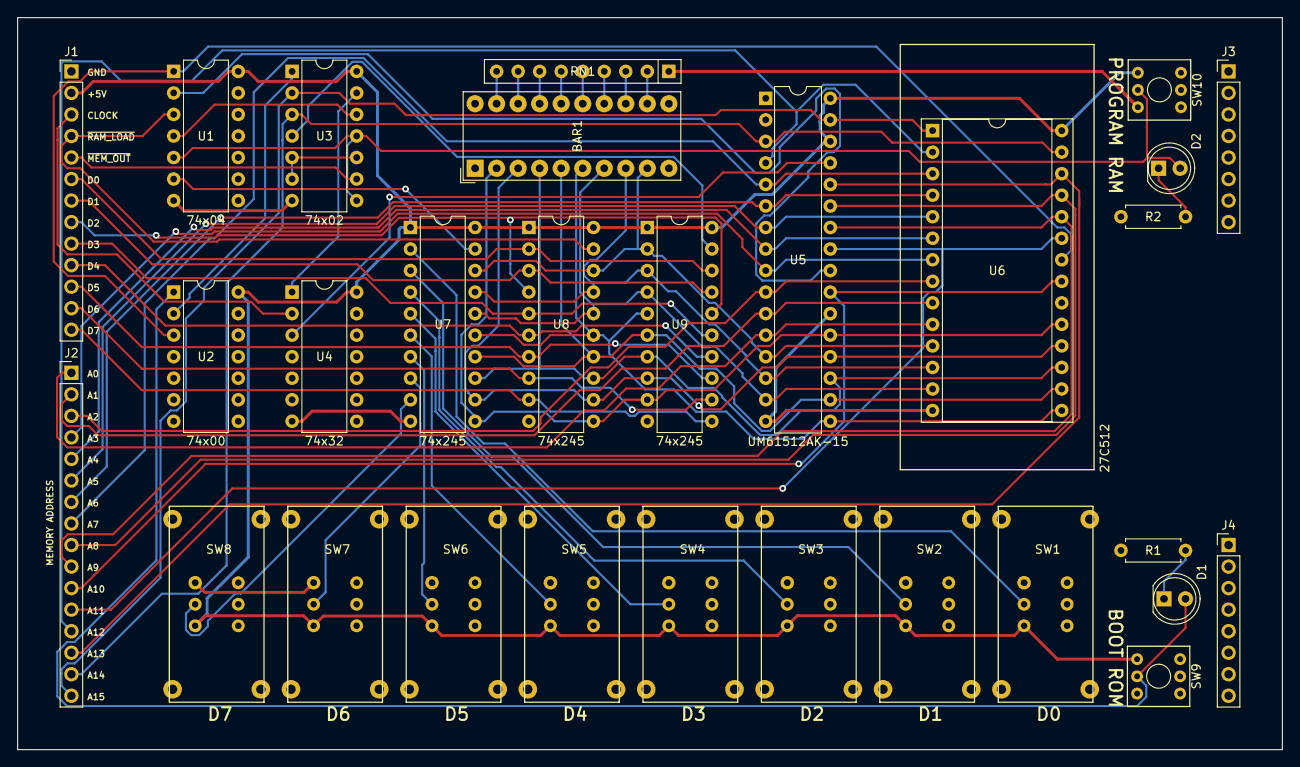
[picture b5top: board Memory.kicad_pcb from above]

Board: 2 copper layers, 149.2 x 86.4 mm, 29 parts (0 on the bottom side), 66 nets.

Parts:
BAR1: HDSP-4830_2; HDSP-4830
D1, D2: LED; LED_D5.0mm
J1: Conn_01x13_Male; PinHeader_1x13_P2.54mm_Vertical
J2: Conn_01x16_Male; PinHeader_1x16_P2.54mm_Vertical
J3, J4: Conn_01x08_Male; PinHeader_1x08_P2.54mm_Vertical
R1, R2: 470; R_Axial_DIN0207_L6.3mm_D2.5mm_P7.62mm_Horizontal
RN1: 470; R_Array_SIP9
SW1, SW2, SW3, SW4, SW5, SW6, SW7, SW8: SW_DPDT_x2; FlipSwitch
SW9, SW10: SW_DPDT_x2; Switch
U1: 74x04; DIP-14_W7.62mm
U2: 74x00; DIP-14_W7.62mm
U3: 74x02; DIP-14_W7.62mm
U4: 74x32; DIP-14_W7.62mm
U5: UM61512AK-15; DIP-32_W7.62mm
U6: 27C512; ZIF-28_Socket
U7, U8, U9: 74x245; DIP-20_W7.62mm

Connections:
+5V: J1.2, SW1.3, SW2.3, SW3.3, SW4.3, SW5.3, SW6.3, SW7.3, SW8.3, SW9.3, SW10.3, U1.14, U2.14, U3.14, U4.14, U5.30, U5.32, U6.28, U7.1, U7.20, U8.1, U8.20, U9.1, U9.20
BOOT_ROM: D1.2, SW9.2, U2.1
CLOCK: J1.3, U4.2
DATA_BUS0: J1.6, U8.2, U9.18
DATA_BUS1: J1.7, U8.3, U9.17
DATA_BUS2: J1.8, U8.4, U9.16
DATA_BUS3: J1.9, U8.5, U9.15
DATA_BUS4: J1.10, U8.6, U9.14
DATA_BUS5: J1.11, U8.7, U9.13
DATA_BUS6: J1.12, U8.8, U9.12
DATA_BUS7: J1.13, U8.9, U9.11
GND: J1.1, R1.1, R2.1, RN1.1, SW1.1, SW2.1, SW3.1, SW4.1, SW5.1, SW6.1, SW7.1, SW8.1, SW9.1, SW10.1, U1.7, U2.7, U3.7, U4.7, U5.16, U5.22, U6.14, U6.20, U7.10, U8.10, U9.10
MANUAL_D0: SW1.2, U7.2
MANUAL_D1: SW2.2, U7.3
MANUAL_D2: SW3.2, U7.4
MANUAL_D3: SW4.2, U7.5
MANUAL_D4: SW5.2, U7.6
MANUAL_D5: SW6.2, U7.7
MANUAL_D6: SW7.2, U7.8
MANUAL_D7: SW8.2, U7.9
unnamed: BAR1.2, U5.21, U6.19, U7.11, U8.11, U9.9
unnamed: BAR1.3, U5.20, U6.18, U7.12, U8.12, U9.8
unnamed: BAR1.4, U5.19, U6.17, U7.13, U8.13, U9.7
unnamed: BAR1.5, U5.18, U6.16, U7.14, U8.14, U9.6
unnamed: BAR1.6, U5.17, U6.15, U7.15, U8.15, U9.5
unnamed: BAR1.7, U5.15, U6.13, U7.16, U8.16, U9.4
unnamed: BAR1.8, U5.14, U6.12, U7.17, U8.17, U9.3
unnamed: BAR1.9, U5.13, U6.11, U7.18, U8.18, U9.2
unnamed: BAR1.12, RN1.2
unnamed: BAR1.13, RN1.3
unnamed: BAR1.14, RN1.4
unnamed: BAR1.15, RN1.5
unnamed: BAR1.16, RN1.6
unnamed: BAR1.17, RN1.7
unnamed: BAR1.18, RN1.8
unnamed: BAR1.19, RN1.9
unnamed: D1.1, R1.2
unnamed: D2.1, R2.2
unnamed: J2.1, U5.12, U6.10
unnamed: J2.2, U5.11, U6.9
unnamed: J2.3, U5.10, U6.8
unnamed: J2.4, U5.9, U6.7
unnamed: J2.5, U5.8, U6.6
unnamed: J2.6, U5.7, U6.5
unnamed: J2.7, U5.6, U6.4
unnamed: J2.8, U5.5, U6.3
unnamed: J2.9, U5.27, U6.25
unnamed: J2.10, U5.26, U6.24
unnamed: J2.11, U5.23, U6.21
unnamed: J2.12, U5.25, U6.23
unnamed: J2.13, U5.4, U6.2
unnamed: J2.14, U5.28, U6.26
unnamed: J2.15, U3.3, U5.3, U6.27
unnamed: J2.16, U3.2, U5.31, U6.1
unnamed: U1.4, U3.12
unnamed: U1.6, U7.19
unnamed: U2.2, U3.1
unnamed: U3.5, U3.6, U3.10
unnamed: U3.13, U4.1
PROGRAM_RAM: D2.2, SW10.2, U1.5, U3.8, U3.11
~DATA_OUT: U3.4, U9.19
~MEM_OUT: J1.5, U3.9
~RAM_LOAD: J1.4, U1.3, U8.19
~RAM_OE: U1.2, U5.24
~RAM_WE: U4.3, U5.29
~ROM_OE: U1.1, U2.3, U6.22

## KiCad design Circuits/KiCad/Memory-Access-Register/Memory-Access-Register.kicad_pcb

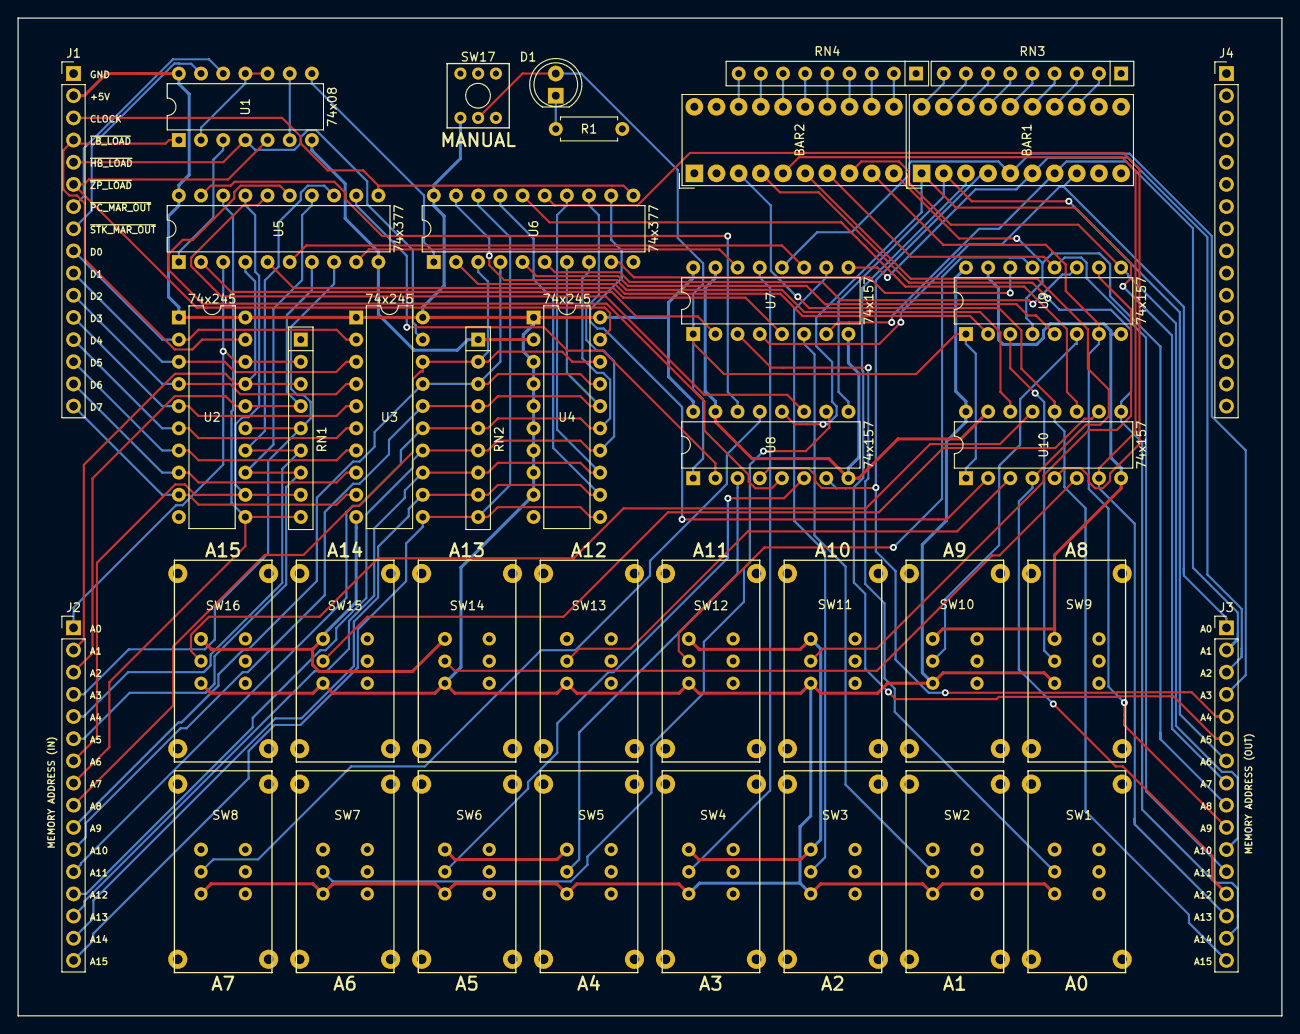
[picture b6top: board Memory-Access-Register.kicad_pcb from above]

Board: 2 copper layers, 144.8 x 114.3 mm, 39 parts (0 on the bottom side), 102 nets.

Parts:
BAR1, BAR2: HDSP-4830_2; HDSP-4830
D1: LED; LED_D5.0mm
J1, J2, J3, J4: Conn_01x16_Male; PinHeader_1x16_P2.54mm_Vertical
R1: 470; R_Axial_DIN0207_L6.3mm_D2.5mm_P7.62mm_Horizontal
RN1, RN2: 10K; R_Array_SIP9
RN3, RN4: 470; R_Array_SIP9
SW1, SW2, SW3, SW4, SW5, SW6, SW7, SW8, SW9, SW10, SW11, SW12, SW13, SW14, SW15, SW16: SW_DPDT_x2; FlipSwitch
SW17: SW_DPDT_x2; Switch
U1: 74x08; DIP-14_W7.62mm
U2, U3, U4: 74x245; DIP-20_W7.62mm
U5, U6: 74x377; DIP-20_W7.62mm
U7, U8, U9, U10: 74x157; DIP-16_W7.62mm

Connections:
+5V: J1.2, SW1.3, SW2.3, SW3.3, SW4.3, SW5.3, SW6.3, SW7.3, SW8.3, SW9.3, SW10.3, SW11.3, SW12.3, SW13.3, SW14.3, SW15.3, SW16.3, SW17.3, U1.14, U2.1, U2.20, U3.1, U3.20, U4.1, U4.3, U4.4, U4.5, U4.6, U4.7, U4.8, U4.9, U4.20, U5.20, U6.20, U7.16, U8.16, U9.16, U10.16
CLOCK: J1.3, U5.11, U6.11
DATA_BUS0: J1.9, U2.2, U3.2
DATA_BUS1: J1.10, U2.3, U3.3
DATA_BUS2: J1.11, U2.4, U3.4
DATA_BUS3: J1.12, U2.5, U3.5
DATA_BUS4: J1.13, U2.6, U3.6
DATA_BUS5: J1.14, U2.7, U3.7
DATA_BUS6: J1.15, U2.8, U3.8
DATA_BUS7: J1.16, U2.9, U3.9
GND: J1.1, R1.1, RN1.1, RN2.1, RN3.1, RN4.1, SW1.1, SW2.1, SW3.1, SW4.1, SW5.1, SW6.1, SW7.1, SW8.1, SW9.1, SW10.1, SW11.1, SW12.1, SW13.1, SW14.1, SW15.1, SW16.1, SW17.1, U1.7, U2.10, U3.10, U4.2, U4.10, U5.10, U6.10, U7.8, U7.15, U8.8, U8.15, U9.8, U9.15, U10.8, U10.15
MANUAL_A0: SW1.2, U7.3
MANUAL_A1: SW2.2, U7.6
MANUAL_A2: SW3.2, U7.10
MANUAL_A3: SW4.2, U7.13
MANUAL_A4: SW5.2, U8.3
MANUAL_A5: SW6.2, U8.6
MANUAL_A6: SW7.2, U8.10
MANUAL_A7: SW8.2, U8.13
MANUAL_A8: SW9.2, U9.3
MANUAL_A9: SW10.2, U9.6
MANUAL_A10: SW11.2, U9.10
MANUAL_A11: SW12.2, U9.13
MANUAL_A12: SW13.2, U10.3
MANUAL_A13: SW14.2, U10.6
MANUAL_A14: SW15.2, U10.10
MANUAL_A15: SW16.2, U10.13
MANUAL_INPUT: D1.2, SW17.2, U7.1, U8.1, U9.1, U10.1
unnamed: BAR1.1, J3.8, U8.12
unnamed: BAR1.2, J3.7, U8.9
unnamed: BAR1.3, J3.6, U8.7
unnamed: BAR1.4, J3.5, U8.4
unnamed: BAR1.5, J3.4, U7.12
unnamed: BAR1.6, J3.3, U7.9
unnamed: BAR1.7, J3.2, U7.7
unnamed: BAR1.8, J3.1, U7.4
unnamed: BAR1.13, RN3.2
unnamed: BAR1.14, RN3.3
unnamed: BAR1.15, RN3.4
unnamed: BAR1.16, RN3.5
unnamed: BAR1.17, RN3.6
unnamed: BAR1.18, RN3.7
unnamed: BAR1.19, RN3.8
unnamed: BAR1.20, RN3.9
unnamed: BAR2.3, J3.16, U10.12
unnamed: BAR2.4, J3.15, U10.9
unnamed: BAR2.5, J3.14, U10.7
unnamed: BAR2.6, J3.13, U10.4
unnamed: BAR2.7, J3.12, U9.12
unnamed: BAR2.8, J3.11, U9.9
unnamed: BAR2.9, J3.10, U9.7
unnamed: BAR2.10, J3.9, U9.4
unnamed: BAR2.11, RN4.2
unnamed: BAR2.12, RN4.3
unnamed: BAR2.13, RN4.4
unnamed: BAR2.14, RN4.5
unnamed: BAR2.15, RN4.6
unnamed: BAR2.16, RN4.7
unnamed: BAR2.17, RN4.8
unnamed: BAR2.18, RN4.9
unnamed: D1.1, R1.2
unnamed: J2.1, RN1.2, U2.18, U5.3
unnamed: J2.2, RN1.3, U2.17, U5.4
unnamed: J2.3, RN1.4, U2.16, U5.7
unnamed: J2.4, RN1.5, U2.15, U5.8
unnamed: J2.5, RN1.6, U2.14, U5.13
unnamed: J2.6, RN1.7, U2.13, U5.14
unnamed: J2.7, RN1.8, U2.12, U5.17
unnamed: J2.8, RN1.9, U2.11, U5.18
unnamed: J2.9, RN2.2, U3.18, U4.18, U6.3
unnamed: J2.10, RN2.3, U3.17, U4.17, U6.4
unnamed: J2.11, RN2.4, U3.16, U4.16, U6.7
unnamed: J2.12, RN2.5, U3.15, U4.15, U6.8
unnamed: J2.13, RN2.6, U3.14, U4.14, U6.13
unnamed: J2.14, RN2.7, U3.13, U4.13, U6.14
unnamed: J2.15, RN2.8, U3.12, U4.12, U6.17
unnamed: J2.16, RN2.9, U3.11, U4.11, U6.18
unnamed: U1.6, U1.9
unnamed: U1.2, U1.10, U1.11
unnamed: U5.2, U7.2
unnamed: U5.5, U7.5
unnamed: U5.6, U7.11
unnamed: U5.9, U7.14
unnamed: U5.12, U8.2
unnamed: U5.15, U8.5
unnamed: U5.16, U8.11
unnamed: U5.19, U8.14
unnamed: U6.2, U9.2
unnamed: U6.5, U9.5
unnamed: U6.6, U9.11
unnamed: U6.9, U9.14
unnamed: U6.12, U10.2
unnamed: U6.15, U10.5
unnamed: U6.16, U10.11
unnamed: U6.19, U10.14
~HB_LOAD: J1.5, U1.4, U3.19
~HIGH_LOAD: U1.8, U6.1
~LB_LOAD: J1.4, U1.1, U2.19
~LOW_LOAD: U1.3, U5.1
~PC_MAR_OUT: J1.7, U1.12
~STK_MAR_OUT: J1.8, U1.13
~ZP_LOAD: J1.6, U1.5, U4.19
